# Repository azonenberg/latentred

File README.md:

# latentred
Open hardware 48x 1000baseT + 2x 25G SFP28 Ethernet switch

Originally located in azonenberg/latentpacket but moved out to avoid monorepo bloat.

High level architecture:
* IBC (x1): 48V -> 12V intermediate bus converter. Not in this repo, see https://github.com/azonenberg/common-ibc
* Line card (x2): 24 10/100/1000 baseT ports, driven by two VSC8512 12-port PHYs
* Switch engine (x1): Kintex UltraScale+ FPGA (XCKU3P or 5P in FFVB676), STM32H735 (tentatively), packet buffer SRAM, 2x 25G SFP28 uplink

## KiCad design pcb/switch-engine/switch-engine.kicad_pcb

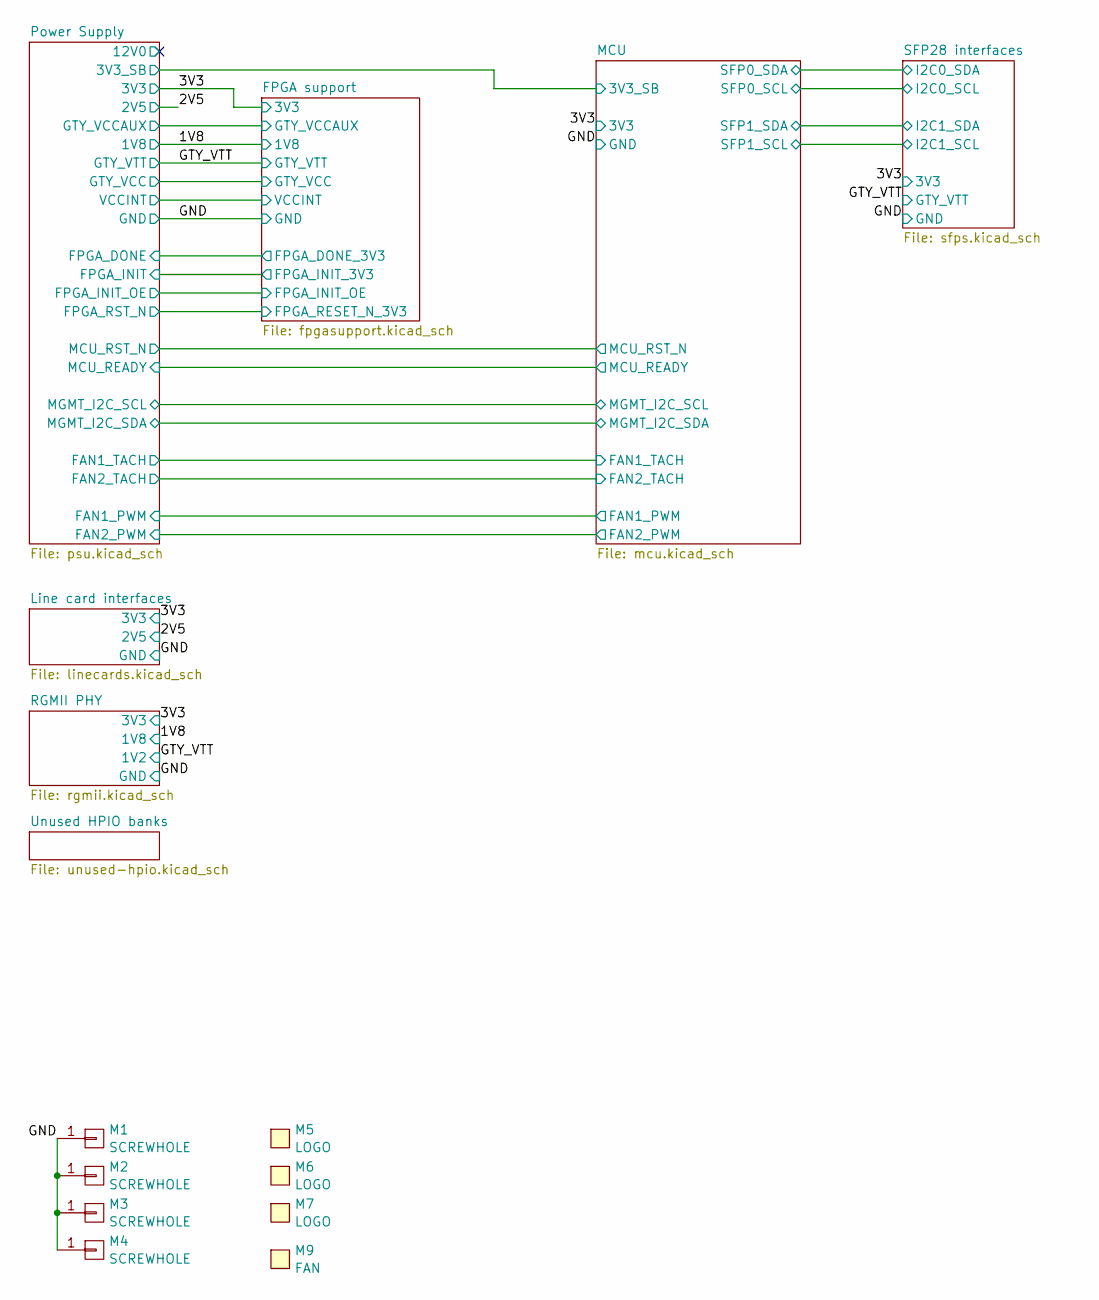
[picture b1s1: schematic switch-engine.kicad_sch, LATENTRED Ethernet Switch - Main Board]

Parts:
M1, M2, M3, M4: SCREWHOLE; MECHANICAL_CLEARANCEHOLE_4_40
M5: LOGO; LONGTHING-1200DPI
M6: LOGO; Logo_silk_OSHW_6x6mm
M7: LOGO; Logo_silk_WEEE_3.4x5mm
M9: FAN; FAN_DELTA_EFB0412VHD-SP05

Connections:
/GND: M1.1, M2.1, M3.1, M4.1; also elsewhere on the board

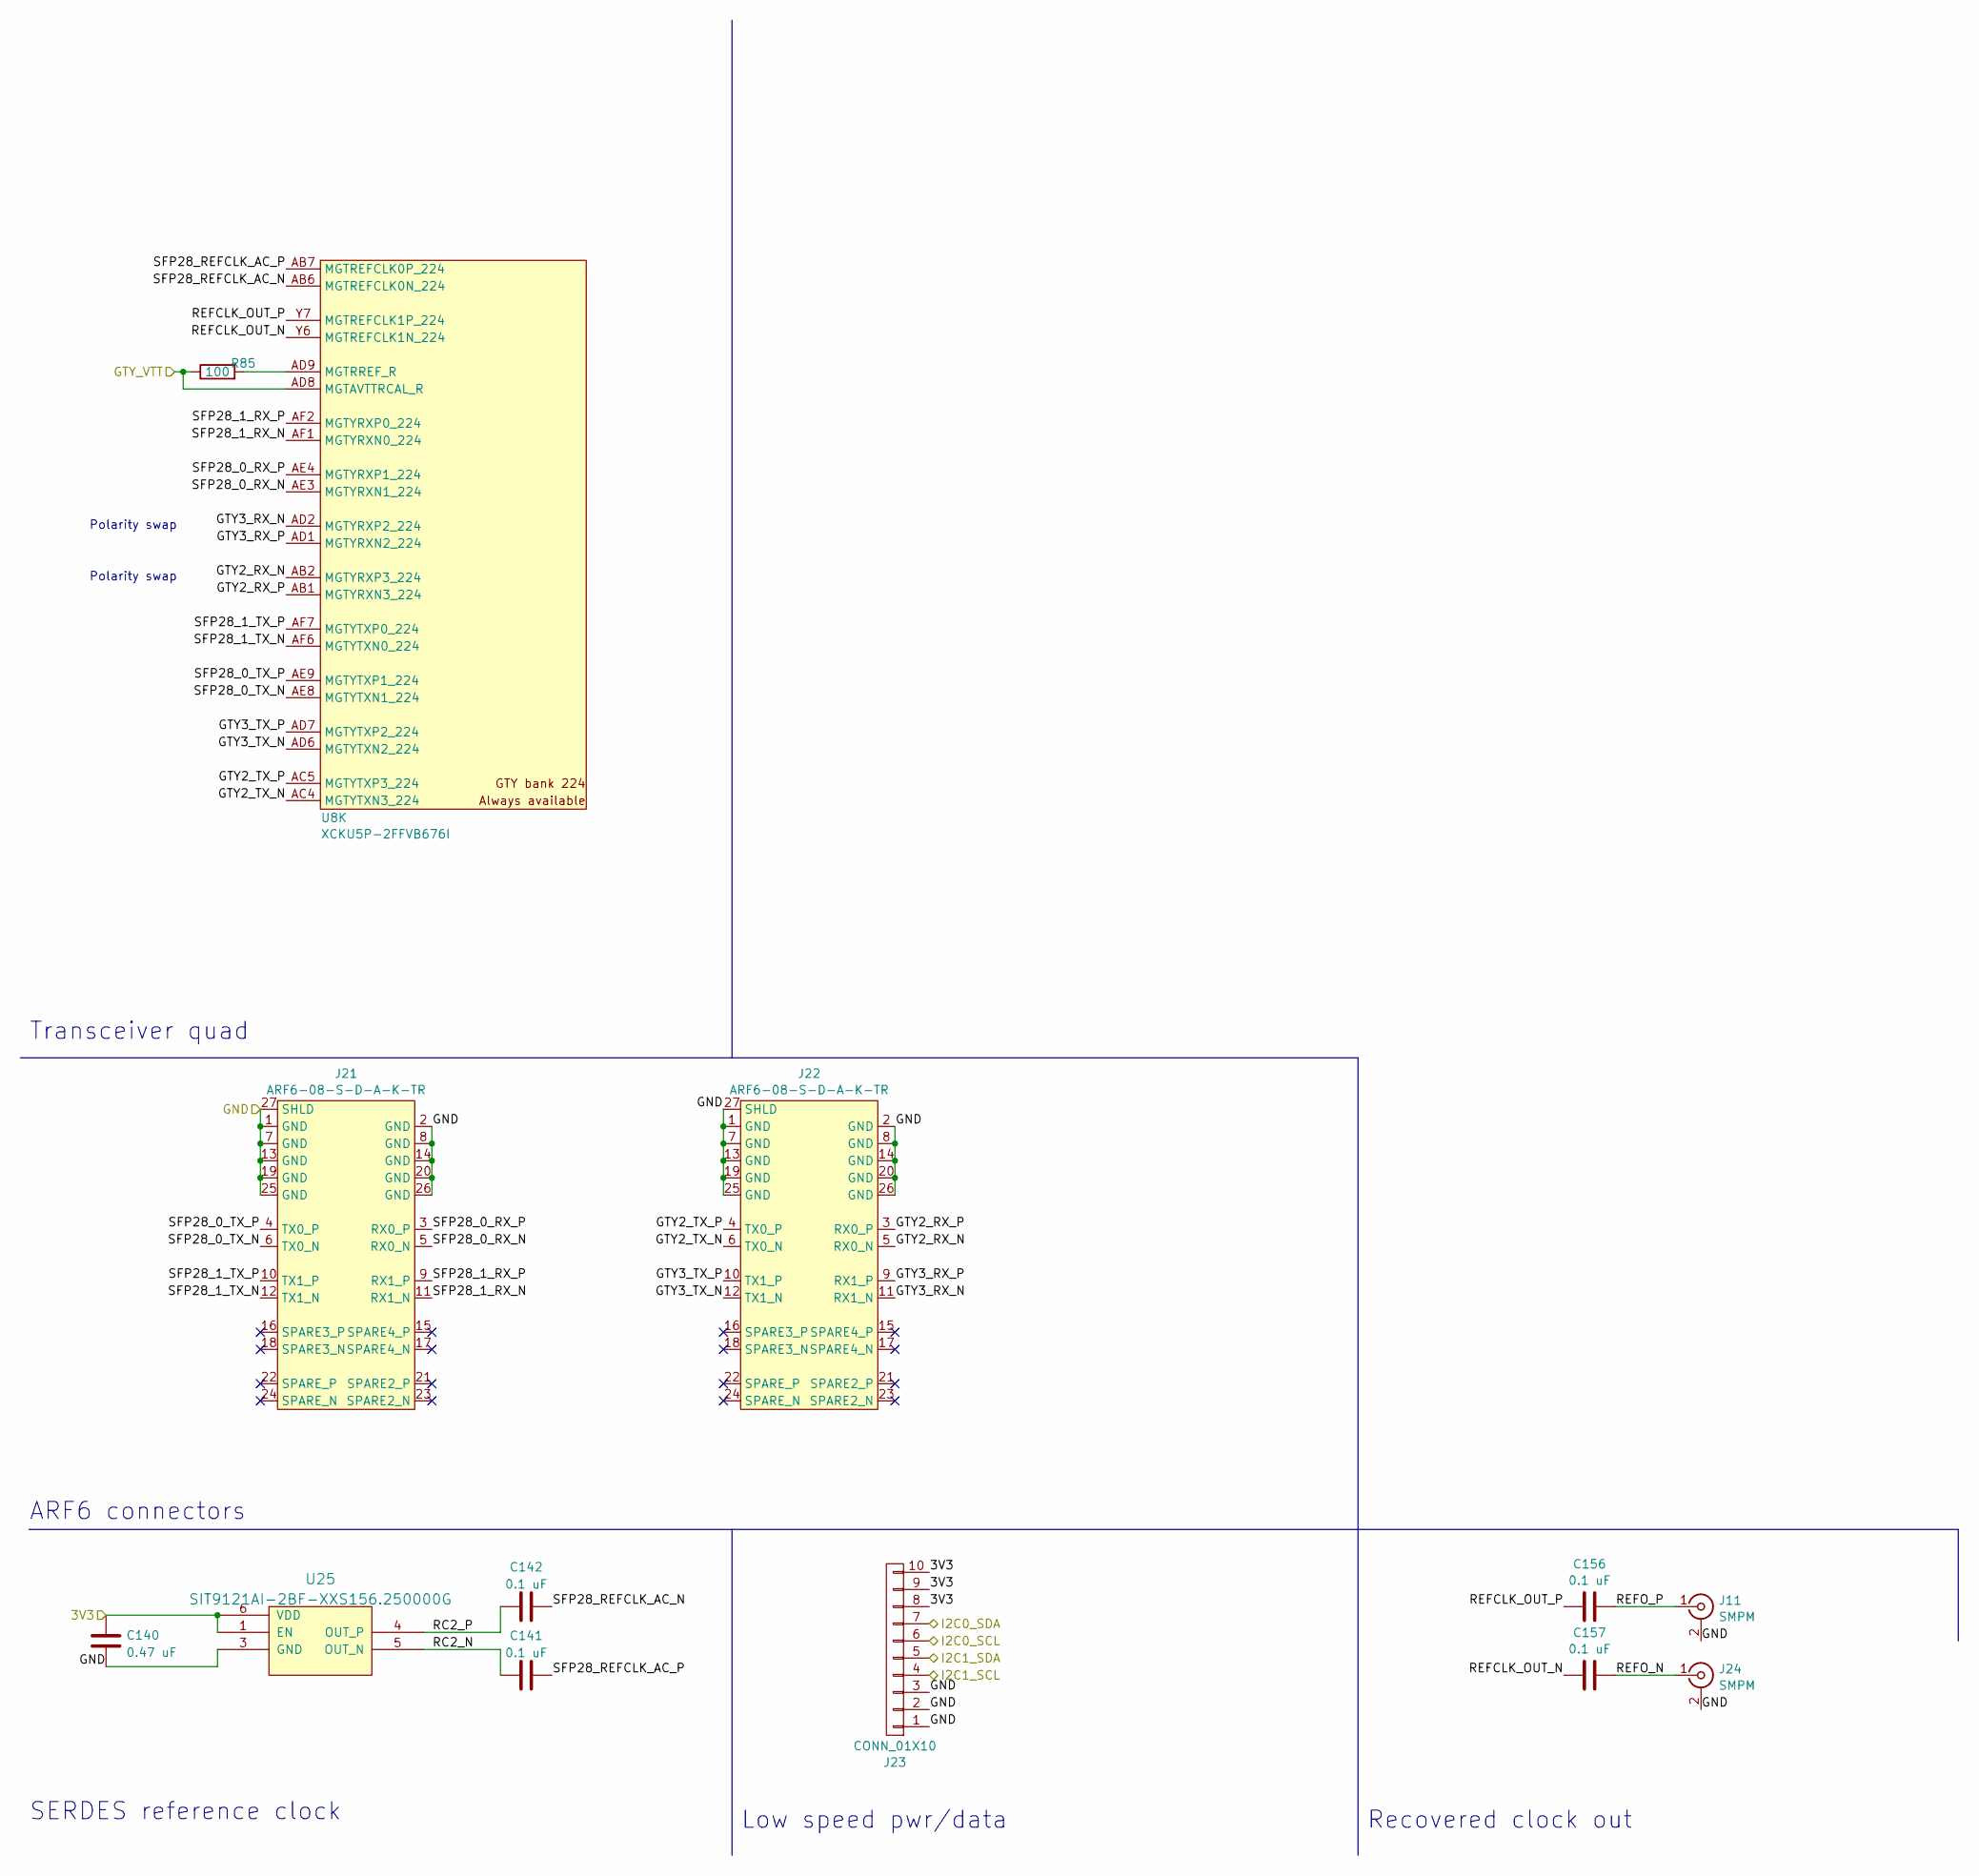
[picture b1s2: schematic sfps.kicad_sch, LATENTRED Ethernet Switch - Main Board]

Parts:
C140: 0.47 uF; EIA_0402_CAP_NOSILK
C141, C142, C156, C157: 0.1 uF; EIA_0402_CAP_NOSILK
J11, J24: SMPM; CONN_SMPM_AMPHENOL_C925-197J-51PT
J21, J22: ARF6-08-S-D-A-K-TR; CONN_SAMTEC_ARF6-08-S-D-A-K-TR
J23: CONN_01X10; CONN_MOLEX_PICOBLADE_10POS_0532611071
R85: 100; EIA_0402_RES_NOSILK
U8: XCKU5P-2FFVB676I; BGA_676_27x27_FULLARRAY_1MM_FFG676
U25: SIT9121AI-2BF-XXS156.250000G; OSCILLATOR_LVDS_3.2x2.5

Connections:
/3V3: C140.1, J23.8, J23.9, J23.10, U25.1 (EN), U25.6 (VDD); also elsewhere on the board
/GND: C140.2, J11.2 (Ext), J21.1 (GND), J21.2 (GND), J21.7 (GND), J21.8 (GND), J21.13 (GND), J21.14 (GND), J21.19 (GND), J21.20 (GND), J21.25 (GND), J21.26 (GND), J21.27 (SHLD), J22.1 (GND), J22.2 (GND), J22.7 (GND), J22.8 (GND), J22.13 (GND), J22.14 (GND), J22.19 (GND), J22.20 (GND), J22.25 (GND), J22.26 (GND), J22.27 (SHLD), J23.1, J23.2, J23.3, J24.2 (Ext), U25.3 (GND); also elsewhere on the board
/GTY_VTT: R85.1, U8.AD8 (MGTAVTTRCAL_R); also elsewhere on the board
/MCU/SFP0_SCL: J23.6; also elsewhere on the board
/MCU/SFP0_SDA: J23.7; also elsewhere on the board
/MCU/SFP1_SCL: J23.4; also elsewhere on the board
/MCU/SFP1_SDA: J23.5; also elsewhere on the board
/SFP28 interfaces/GTY2_RX_N: J22.5 (RX0_N), U8.AB2 (MGTYRXP3_224)
/SFP28 interfaces/GTY2_RX_P: J22.3 (RX0_P), U8.AB1 (MGTYRXN3_224)
/SFP28 interfaces/GTY2_TX_N: J22.6 (TX0_N), U8.AC4 (MGTYTXN3_224)
/SFP28 interfaces/GTY2_TX_P: J22.4 (TX0_P), U8.AC5 (MGTYTXP3_224)
/SFP28 interfaces/GTY3_RX_N: J22.11 (RX1_N), U8.AD2 (MGTYRXP2_224)
/SFP28 interfaces/GTY3_RX_P: J22.9 (RX1_P), U8.AD1 (MGTYRXN2_224)
/SFP28 interfaces/GTY3_TX_N: J22.12 (TX1_N), U8.AD6 (MGTYTXN2_224)
/SFP28 interfaces/GTY3_TX_P: J22.10 (TX1_P), U8.AD7 (MGTYTXP2_224)
/SFP28 interfaces/RC2_N: C141.1, U25.5 (OUT_N)
/SFP28 interfaces/RC2_P: C142.1, U25.4 (OUT_P)
/SFP28 interfaces/REFCLK_OUT_N: C157.1, U8.Y6 (MGTREFCLK1N_224)
/SFP28 interfaces/REFCLK_OUT_P: C156.1, U8.Y7 (MGTREFCLK1P_224)
/SFP28 interfaces/REFO_N: C157.2, J24.1 (In)
/SFP28 interfaces/REFO_P: C156.2, J11.1 (In)
/SFP28 interfaces/SFP28_0_RX_N: J21.5 (RX0_N), U8.AE3 (MGTYRXN1_224)
/SFP28 interfaces/SFP28_0_RX_P: J21.3 (RX0_P), U8.AE4 (MGTYRXP1_224)
/SFP28 interfaces/SFP28_0_TX_N: J21.6 (TX0_N), U8.AE8 (MGTYTXN1_224)
/SFP28 interfaces/SFP28_0_TX_P: J21.4 (TX0_P), U8.AE9 (MGTYTXP1_224)
/SFP28 interfaces/SFP28_1_RX_N: J21.11 (RX1_N), U8.AF1 (MGTYRXN0_224)
/SFP28 interfaces/SFP28_1_RX_P: J21.9 (RX1_P), U8.AF2 (MGTYRXP0_224)
/SFP28 interfaces/SFP28_1_TX_N: J21.12 (TX1_N), U8.AF6 (MGTYTXN0_224)
/SFP28 interfaces/SFP28_1_TX_P: J21.10 (TX1_P), U8.AF7 (MGTYTXP0_224)
/SFP28 interfaces/SFP28_REFCLK_AC_N: C142.2, U8.AB6 (MGTREFCLK0N_224)
/SFP28 interfaces/SFP28_REFCLK_AC_P: C141.2, U8.AB7 (MGTREFCLK0P_224)
unnamed: R85.2, U8.AD9 (MGTRREF_R)

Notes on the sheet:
Transceiver quad
Low speed pwr/data
Polarity swap
Recovered clock out
ARF6 connectors
SERDES reference clock

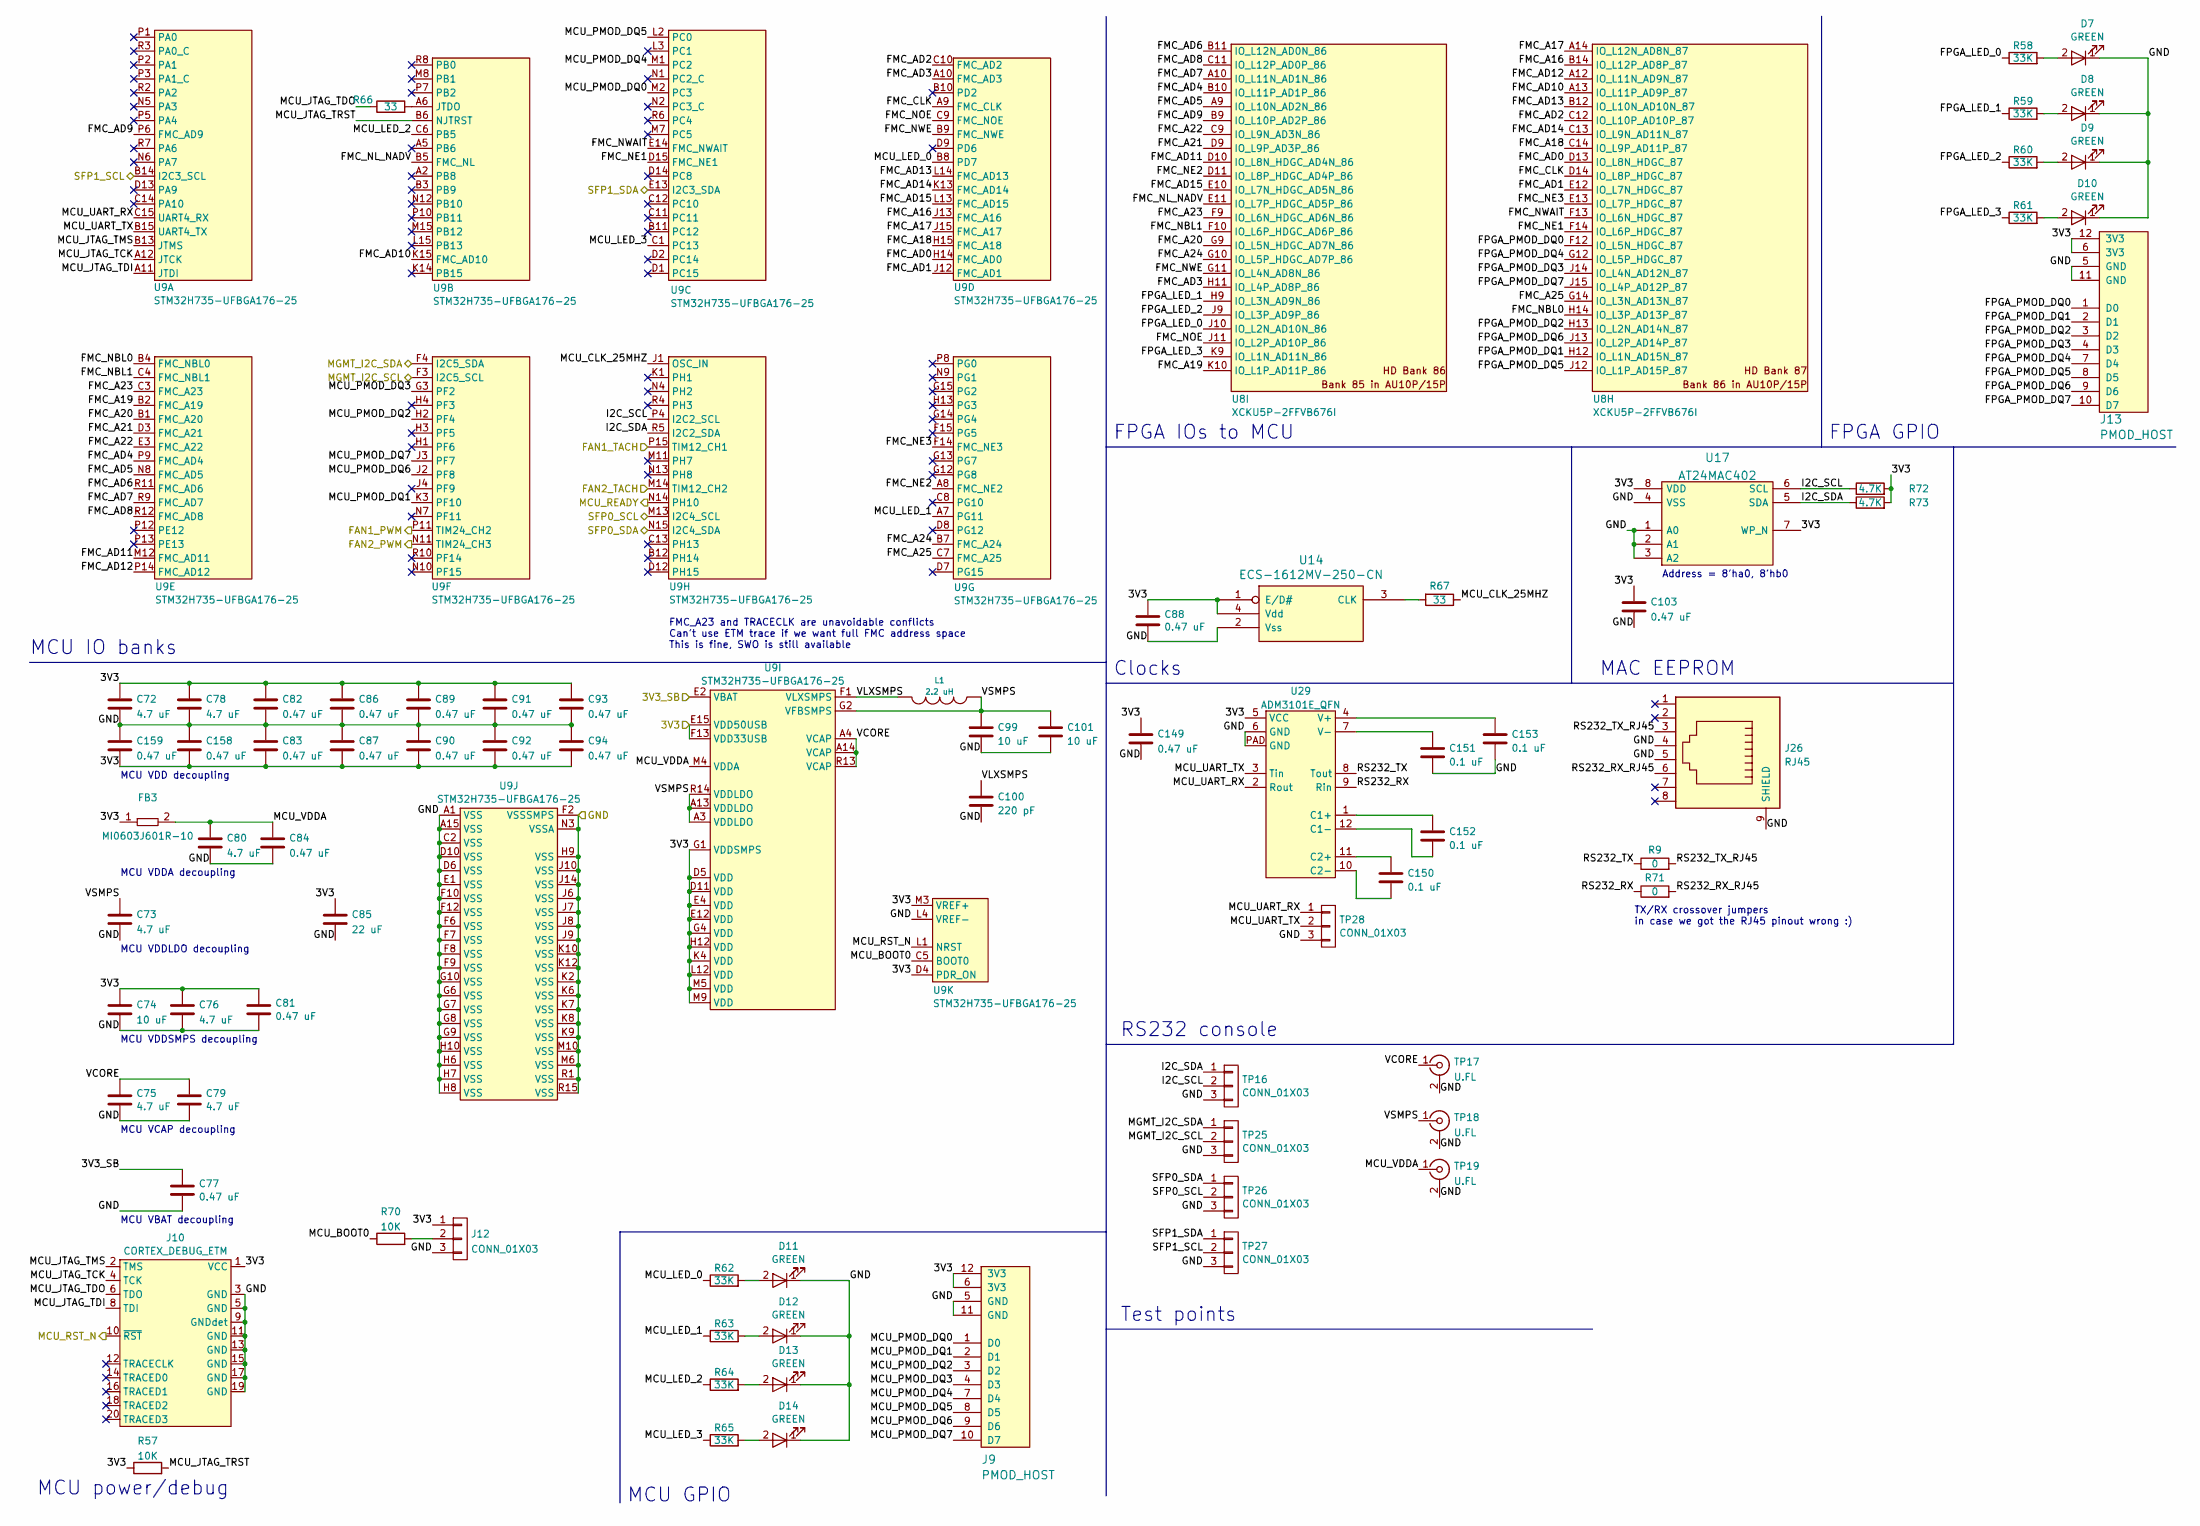
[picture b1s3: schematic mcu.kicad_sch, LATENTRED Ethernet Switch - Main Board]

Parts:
C72, C73, C75, C76, C78, C79, C80: 4.7 uF; EIA_0603_CAP_NOSILK
C74, C99, C101: 10 uF; EIA_0805_CAP_NOSILK
C77, C82, C83, C84, C86, C89, C90, C92, C93, C94: 0.47 uF; EIA_0201_CAP_NOSILK
C81, C87, C88, C91, C103, C149, C158, C159: 0.47 uF; EIA_0402_CAP_NOSILK
C85: 22 uF; EIA_0805_CAP_NOSILK
C100: 220 pF; EIA_0402_CAP_NOSILK
C150, C151, C152, C153: 0.1 uF; EIA_0402_CAP_NOSILK
D7, D8, D9, D10, D11, D12, D13, D14: GREEN; EIA_0402_LED
FB3: MI0603J601R-10; EIA_0603_INDUCTOR_NOSILK
J9, J13: PMOD_HOST; CONN_HEADER_2.54MM_2x6_RA_PMOD_HOST
J10: CORTEX_DEBUG_ETM; CONN_HEADER_1.27MM_2x10_SMT_SAMTEC_FTSH-110-01-L-DV-K
J12: CONN_01X03; CONN_HEADER_2.54MM_1x3
J26: RJ45; CONN_RJ45_BELSTEWART_SS-7188S-A-PG4-1-BA-xx
L1: 2.2 uH; EIA_1210_CAP_NOSILK
R9, R71: 0; EIA_0402_RES_NOSILK
R57, R70: 10K; EIA_0402_RES_NOSILK
R58, R59, R60, R61, R62, R63, R64, R65: 33K; EIA_0402_RES_NOSILK
R66, R67: 33; EIA_0402_RES_NOSILK
R72, R73: 4.7K; EIA_0402_RES_NOSILK
TP16, TP25, TP26, TP27, TP28: CONN_01X03; CONN_HEADER_2.54MM_1x3
TP17, TP18, TP19: U.FL; CONN_U.FL_TE_1909763-1
U8: XCKU5P-2FFVB676I; BGA_676_27x27_FULLARRAY_1MM_FFG676
U9: STM32H735-UFBGA176-25; BGA_201_10x10_DEPOP_0.65MM_OSHPARK
U14: ECS-1612MV-250-CN; OSCILLATOR_1.6x1.2
U17: AT24MAC402; DFN_8_0.5MM_2x3MM_TALL
U29: ADM3101E_QFN; QFN_12_0.5MM_3x3MM

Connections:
/3V3: C72.1, C74.1, C76.1, C78.1, C81.1, C82.1, C83.2, C85.1, C86.1, C87.2, C88.1, C89.1, C90.2, C91.1, C92.2, C93.1, C94.2, C103.1, C149.1, C158.2, C159.2, FB3.1, J9.6 (3V3), J9.12 (3V3), J10.1 (VCC), J12.1, J13.6 (3V3), J13.12 (3V3), R57.1, R72.2, R73.2, U9.D4 (PDR_ON), U9.D5 (VDD), U9.D11 (VDD), U9.E4 (VDD), U9.E12 (VDD), U9.E15 (VDD50USB), U9.F13 (VDD33USB), U9.G1 (VDDSMPS), U9.G4 (VDD), U9.H12 (VDD), U9.K4 (VDD), U9.L12 (VDD), U9.M3 (VREF+), U9.M5 (VDD), U9.M9 (VDD), U14.1 (E/D#), U14.4 (Vdd), U17.7 (WP_N), U17.8 (VDD), U29.5 (VCC); also elsewhere on the board
/GND: C72.2, C73.2, C74.2, C75.2, C76.2, C77.2, C78.2, C79.2, C80.2, C81.2, C82.2, C83.1, C84.2, C85.2, C86.2, C87.1, C88.2, C89.2, C90.1, C91.2, C92.1, C93.2, C94.1, C99.2, C100.2, C101.2, C103.2, C149.2, C151.2, C153.2, C158.1, C159.1, D7.1 (K), D8.1 (K), D9.1 (K), D10.1 (K), D11.1 (K), D12.1 (K), D13.1 (K), D14.1 (K), J9.5 (GND), J9.11 (GND), J10.3 (GND), J10.5 (GND), J10.9 (GNDdet), J10.11 (GND), J10.13 (GND), J10.15 (GND), J10.17 (GND), J10.19 (GND), J12.3, J13.5 (GND), J13.11 (GND), J26.4, J26.5, J26.9 (SHIELD), TP16.3, TP17.2 (Ext), TP18.2 (Ext), TP19.2 (Ext), TP25.3, TP26.3, TP27.3, TP28.3, U9.A1 (VSS), U9.A15 (VSS), U9.C2 (VSS), U9.D6 (VSS), U9.D10 (VSS), U9.E1 (VSS), U9.F2 (VSSSMPS), U9.F6 (VSS), U9.F7 (VSS), U9.F8 (VSS), U9.F9 (VSS), U9.F10 (VSS), U9.F12 (VSS), U9.G6 (VSS), U9.G7 (VSS), U9.G8 (VSS), U9.G9 (VSS), U9.G10 (VSS), U9.H6 (VSS), U9.H7 (VSS), U9.H8 (VSS), U9.H9 (VSS), U9.H10 (VSS), U9.J6 (VSS), U9.J7 (VSS), U9.J8 (VSS), U9.J9 (VSS), U9.J10 (VSS), U9.J14 (VSS), U9.K2 (VSS), U9.K6 (VSS), U9.K7 (VSS), U9.K8 (VSS), U9.K9 (VSS), U9.K10 (VSS), U9.K12 (VSS), U9.L4 (VREF-), U9.M6 (VSS), U9.M10 (VSS), U9.N3 (VSSA), U9.R1 (VSS), U9.R15 (VSS), U14.2 (Vss), U17.1 (A0), U17.2 (A1), U17.3 (A2), U17.4 (VSS), U29.6 (GND), U29.PAD (GND); also elsewhere on the board
/MCU/3V3_SB: C77.1, U9.E2 (VBAT); also elsewhere on the board
/MCU/FMC_A16: U8.B14 (IO_L12P_AD8P_87), U9.J13 (FMC_A16)
/MCU/FMC_A17: U8.A14 (IO_L12N_AD8N_87), U9.J15 (FMC_A17)
/MCU/FMC_A18: U8.C14 (IO_L9P_AD11P_87), U9.H15 (FMC_A18)
/MCU/FMC_A19: U8.K10 (IO_L1P_AD11P_86), U9.B2 (FMC_A19)
/MCU/FMC_A20: U8.G9 (IO_L5N_HDGC_AD7N_86), U9.B1 (FMC_A20)
/MCU/FMC_A21: U8.D9 (IO_L9P_AD3P_86), U9.D3 (FMC_A21)
/MCU/FMC_A22: U8.C9 (IO_L9N_AD3N_86), U9.E3 (FMC_A22)
/MCU/FMC_A23: U8.F9 (IO_L6N_HDGC_AD6N_86), U9.C3 (FMC_A23)
/MCU/FMC_A24: U8.G10 (IO_L5P_HDGC_AD7P_86), U9.B7 (FMC_A24)
/MCU/FMC_A25: U8.G14 (IO_L3N_AD13N_87), U9.C7 (FMC_A25)
/MCU/FMC_AD0: U8.D13 (IO_L8N_HDGC_87), U9.H14 (FMC_AD0)
/MCU/FMC_AD1: U8.E12 (IO_L7N_HDGC_87), U9.J12 (FMC_AD1)
/MCU/FMC_AD2: U8.C12 (IO_L10P_AD10P_87), U9.C10 (FMC_AD2)
/MCU/FMC_AD3: U8.H11 (IO_L4P_AD8P_86), U9.A10 (FMC_AD3)
/MCU/FMC_AD4: U8.B10 (IO_L11P_AD1P_86), U9.P9 (FMC_AD4)
/MCU/FMC_AD5: U8.A9 (IO_L10N_AD2N_86), U9.N8 (FMC_AD5)
/MCU/FMC_AD6: U8.B11 (IO_L12N_AD0N_86), U9.R11 (FMC_AD6)
/MCU/FMC_AD7: U8.A10 (IO_L11N_AD1N_86), U9.R9 (FMC_AD7)
/MCU/FMC_AD8: U8.C11 (IO_L12P_AD0P_86), U9.R12 (FMC_AD8)
/MCU/FMC_AD9: U8.B9 (IO_L10P_AD2P_86), U9.P6 (FMC_AD9)
/MCU/FMC_AD10: U8.A13 (IO_L11P_AD9P_87), U9.K15 (FMC_AD10)
/MCU/FMC_AD11: U8.D10 (IO_L8N_HDGC_AD4N_86), U9.M12 (FMC_AD11)
/MCU/FMC_AD12: U8.A12 (IO_L11N_AD9N_87), U9.P14 (FMC_AD12)
/MCU/FMC_AD13: U8.B12 (IO_L10N_AD10N_87), U9.L14 (FMC_AD13)
/MCU/FMC_AD14: U8.C13 (IO_L9N_AD11N_87), U9.K13 (FMC_AD14)
/MCU/FMC_AD15: U8.E10 (IO_L7N_HDGC_AD5N_86), U9.L13 (FMC_AD15)
/MCU/FMC_CLK: U8.D14 (IO_L8P_HDGC_87), U9.A9 (FMC_CLK)
/MCU/FMC_NBL0: U8.H14 (IO_L3P_AD13P_87), U9.B4 (FMC_NBL0)
/MCU/FMC_NBL1: U8.F10 (IO_L6P_HDGC_AD6P_86), U9.C4 (FMC_NBL1)
/MCU/FMC_NE1: U8.F14 (IO_L6P_HDGC_87), U9.D15 (FMC_NE1)
/MCU/FMC_NE2: U8.D11 (IO_L8P_HDGC_AD4P_86), U9.A8 (FMC_NE2)
/MCU/FMC_NE3: U8.E13 (IO_L7P_HDGC_87), U9.F14 (FMC_NE3)
/MCU/FMC_NL_NADV: U8.E11 (IO_L7P_HDGC_AD5P_86), U9.B5 (FMC_NL)
/MCU/FMC_NOE: U8.J11 (IO_L2P_AD10P_86), U9.C9 (FMC_NOE)
/MCU/FMC_NWAIT: U8.F13 (IO_L6N_HDGC_87), U9.E14 (FMC_NWAIT)
/MCU/FMC_NWE: U8.G11 (IO_L4N_AD8N_86), U9.B9 (FMC_NWE)
/MCU/FPGA_LED_0: R58.1, U8.J10 (IO_L2N_AD10N_86)
/MCU/FPGA_LED_1: R59.1, U8.H9 (IO_L3N_AD9N_86)
/MCU/FPGA_LED_2: R60.1, U8.J9 (IO_L3P_AD9P_86)
/MCU/FPGA_LED_3: R61.1, U8.K9 (IO_L1N_AD11N_86)
/MCU/FPGA_PMOD_DQ0: J13.1 (D0), U8.F12 (IO_L5N_HDGC_87)
/MCU/FPGA_PMOD_DQ1: J13.2 (D1), U8.H12 (IO_L1N_AD15N_87)
/MCU/FPGA_PMOD_DQ2: J13.3 (D2), U8.H13 (IO_L2N_AD14N_87)
/MCU/FPGA_PMOD_DQ3: J13.4 (D3), U8.J14 (IO_L4N_AD12N_87)
/MCU/FPGA_PMOD_DQ4: J13.7 (D4), U8.G12 (IO_L5P_HDGC_87)
/MCU/FPGA_PMOD_DQ5: J13.8 (D5), U8.J12 (IO_L1P_AD15P_87)
/MCU/FPGA_PMOD_DQ6: J13.9 (D6), U8.J13 (IO_L2P_AD14P_87)
/MCU/FPGA_PMOD_DQ7: J13.10 (D7), U8.J15 (IO_L4P_AD12P_87)
/MCU/I2C_SCL: R72.1, TP16.2, U9.P4 (I2C2_SCL), U17.6 (SCL)
/MCU/I2C_SDA: R73.1, TP16.1, U9.R5 (I2C2_SDA), U17.5 (SDA)
/MCU/MCU_BOOT0: R70.1, U9.C5 (BOOT0)
/MCU/MCU_CLK_25MHZ: R67.1, U9.J1 (OSC_IN)
/MCU/MCU_JTAG_TCK: J10.4 (TCK), U9.A12 (JTCK)
/MCU/MCU_JTAG_TDI: J10.8 (TDI), U9.A11 (JTDI)
/MCU/MCU_JTAG_TDO: J10.6 (TDO), R66.1
/MCU/MCU_JTAG_TMS: J10.2 (TMS), U9.B13 (JTMS)
/MCU/MCU_JTAG_TRST: R57.2, U9.B6 (NJTRST)
/MCU/MCU_LED_0: R62.1, U9.B8 (PD7)
/MCU/MCU_LED_1: R63.1, U9.A7 (PG11)
/MCU/MCU_LED_2: R64.1, U9.C6 (PB5)
/MCU/MCU_LED_3: R65.1, U9.C1 (PC13)
/MCU/MCU_PMOD_DQ0: J9.1 (D0), U9.M2 (PC3)
/MCU/MCU_PMOD_DQ1: J9.2 (D1), U9.K3 (PF10)
/MCU/MCU_PMOD_DQ2: J9.3 (D2), U9.H2 (PF4)
/MCU/MCU_PMOD_DQ3: J9.4 (D3), U9.G3 (PF2)
/MCU/MCU_PMOD_DQ4: J9.7 (D4), U9.M1 (PC2)
/MCU/MCU_PMOD_DQ5: J9.8 (D5), U9.L2 (PC0)
/MCU/MCU_PMOD_DQ6: J9.9 (D6), U9.J2 (PF8)
/MCU/MCU_PMOD_DQ7: J9.10 (D7), U9.J3 (PF7)
/MCU/MCU_READY: U9.N14 (PH10); also elsewhere on the board
/MCU/MCU_RST_N: J10.10 (~RST), U9.L1 (NRST); also elsewhere on the board
/MCU/MCU_UART_RX: TP28.1, U9.C15 (UART4_RX), U29.2 (Rout)
/MCU/MCU_UART_TX: TP28.2, U9.B15 (UART4_TX), U29.3 (Tin)
/MCU/MCU_VDDA: C80.1, C84.1, FB3.2, TP19.1 (In), U9.M4 (VDDA)
/MCU/MGMT_I2C_SCL: TP25.2, U9.F3 (I2C5_SCL); also elsewhere on the board
/MCU/MGMT_I2C_SDA: TP25.1, U9.F4 (I2C5_SDA); also elsewhere on the board
/MCU/RS232_RX: R71.1, U29.9 (Rin)
/MCU/RS232_RX_RJ45: J26.6, R71.2
/MCU/RS232_TX: R9.1, U29.8 (Tout)
/MCU/RS232_TX_RJ45: J26.3, R9.2
/MCU/SFP0_SCL: TP26.2, U9.M13 (I2C4_SCL); also elsewhere on the board
/MCU/SFP0_SDA: TP26.1, U9.N15 (I2C4_SDA); also elsewhere on the board
/MCU/SFP1_SCL: TP27.2, U9.B14 (I2C3_SCL); also elsewhere on the board
/MCU/SFP1_SDA: TP27.1, U9.E13 (I2C3_SDA); also elsewhere on the board
/MCU/VCORE: C75.1, C79.1, TP17.1 (In), U9.A4 (VCAP), U9.A14 (VCAP), U9.R13 (VCAP)
/MCU/VLXSMPS: C100.1, L1.2, U9.F1 (VLXSMPS)
/MCU/VSMPS: C73.1, C99.1, C101.1, L1.1, TP18.1 (In), U9.A3 (VDDLDO), U9.A13 (VDDLDO), U9.G2 (VFBSMPS), U9.R14 (VDDLDO)
/Power Supply/FAN1_PWM: U9.P11 (TIM24_CH2); also elsewhere on the board
/Power Supply/FAN1_TACH: U9.P15 (TIM12_CH1); also elsewhere on the board
/Power Supply/FAN2_PWM: U9.N11 (TIM24_CH3); also elsewhere on the board
/Power Supply/FAN2_TACH: U9.M14 (TIM12_CH2); also elsewhere on the board
unnamed: D7.2 (A), R58.2
unnamed: D8.2 (A), R59.2
unnamed: D9.2 (A), R60.2
unnamed: D10.2 (A), R61.2
unnamed: D11.2 (A), R62.2
unnamed: D12.2 (A), R63.2
unnamed: D13.2 (A), R64.2
unnamed: D14.2 (A), R65.2
unnamed: J12.2, R70.2
unnamed: R66.2, U9.A6 (JTDO)
unnamed: R67.2, U14.3 (CLK)
unnamed: C152.1, U29.1 (C1+)
unnamed: C152.2, U29.12 (C1-)
unnamed: C150.1, U29.11 (C2+)
unnamed: C150.2, U29.10 (C2-)
unnamed: C153.1, U29.4 (V+)
unnamed: C151.1, U29.7 (V-)

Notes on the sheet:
RS232 console
FPGA IOs to MCU
MCU VDD decoupling
MCU VCAP decoupling
Test points
TX/RX crossover jumpers in case we got the RJ45 pinout wrong :)
FPGA GPIO
MCU VDDA decoupling
MCU GPIO
MCU VDDLDO decoupling
MCU VDDSMPS decoupling
MCU VBAT decoupling
MAC EEPROM
Address = 8'ha0, 8'hb0
FMC_A23 and TRACECLK are unavoidable conflicts Can't use ETM trace if we want full FMC address space This is fine, SWO is still available
MCU IO banks
Clocks
MCU power/debug

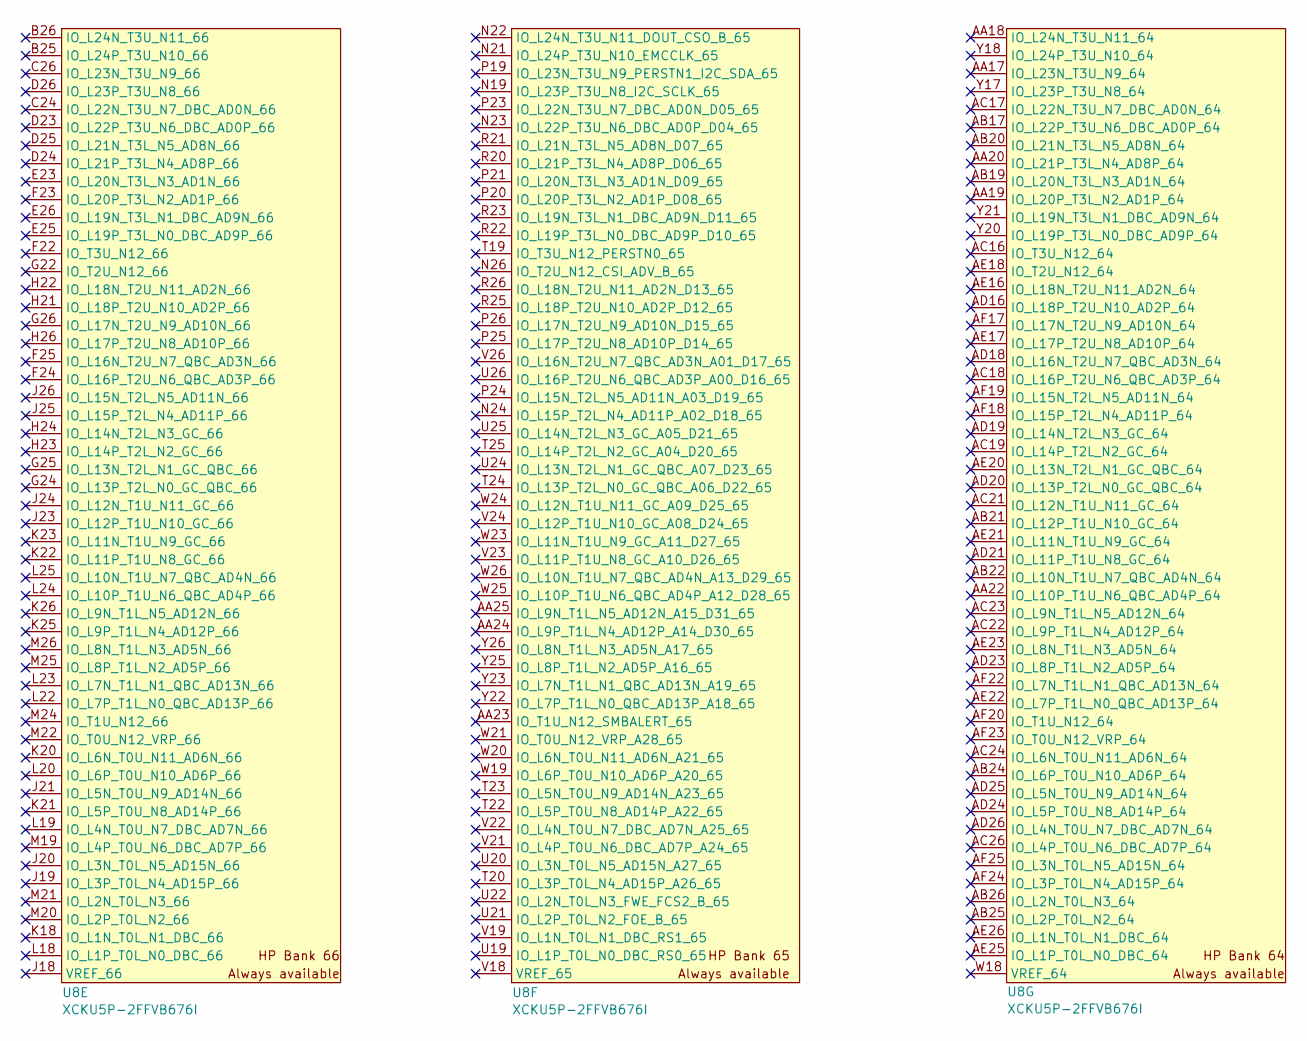
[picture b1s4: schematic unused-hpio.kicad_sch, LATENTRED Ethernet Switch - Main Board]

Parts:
U8: XCKU5P-2FFVB676I; BGA_676_27x27_FULLARRAY_1MM_FFG676
